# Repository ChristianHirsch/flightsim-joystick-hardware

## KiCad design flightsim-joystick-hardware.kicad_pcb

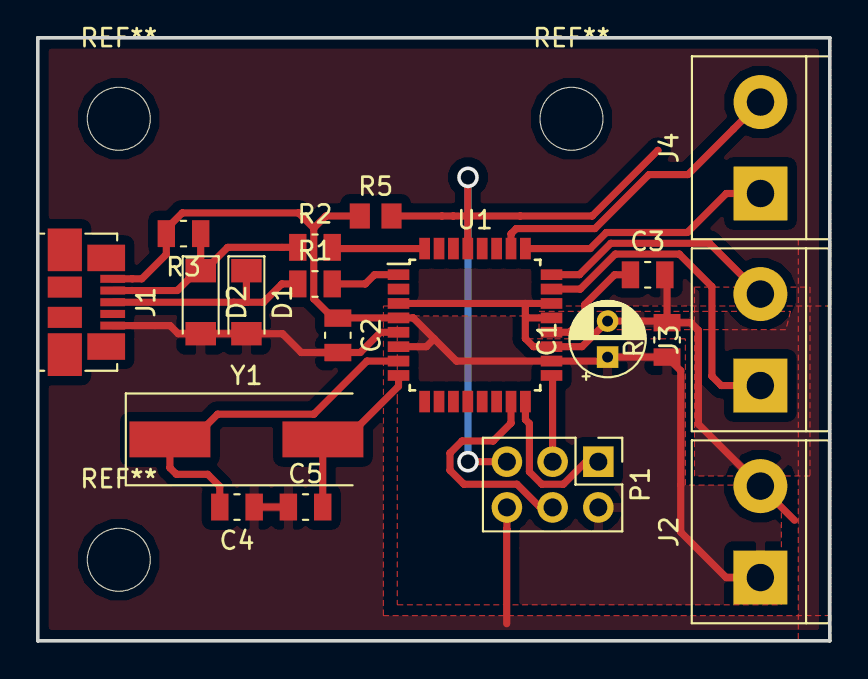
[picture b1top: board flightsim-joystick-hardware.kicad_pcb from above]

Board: 2 copper layers, 44.0 x 33.5 mm, 19 parts (0 on the bottom side), 17 nets.

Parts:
C1: 10µ; CP_Radial_D4.0mm_P2.00mm
C2, C3: 100n; C_0805_2012Metric
C4, C5: 27p; C_0805_2012Metric
D1, D2: D_Zener; D_MiniMELF
J1: USB_OTG; USB_Micro-B_Molex_47346-0001
J2, J3, J4: Conn_01x02; TerminalBlock_bornier-2_P5.08mm
P1: CONN_02X03; PinHeader_2x03_P2.54mm_Vertical
R1, R2: 68; R_0805_2012Metric
R3: 1.5k; R_0805_2012Metric
R4: 56k; R_0805_2012Metric
R5: 10k; R_0805_2012Metric
U1: ATMEGA328P-AU; LQFP-32_7x7mm_P0.8mm
Y1: 12MHz; Crystal_SMD_HC49-SD

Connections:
+5V: C1.1, C2.1, J1.1, J2.1, P1.2, R3.2, R4.1, R5.1, U1.4, U1.6, U1.18
/W_Pos: J4.2, U1.26
/X_Pos: J3.1, U1.23
/Y_Pos: J3.2, U1.24
/Z_Pos: J4.1, U1.25
GND: C1.2, C2.2, C3.2, C4.1, C5.1, D1.2, D2.2, J1.5, J2.2, P1.6, R4.2, U1.3, U1.5, U1.19, U1.21, U1.22
unnamed: C3.1, U1.20
unnamed: C4.2, U1.7, Y1.1
unnamed: C5.2, U1.8, Y1.2
unnamed: D1.1, J1.3, R1.1
unnamed: D2.1, J1.2, R2.1, R3.1
unnamed: P1.1, U1.16
unnamed: P1.3, U1.17
unnamed: P1.4, U1.15
unnamed: P1.5, R5.2, U1.29
USB_DM: R2.2, U1.32
USB_DP: R1.2, U1.1

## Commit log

2018-04-19 add 2 more ADC connectors
